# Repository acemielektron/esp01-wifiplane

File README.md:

# esp01-wifiplane

Here is the modified code and hardware for esp01 running [RAVI_BUTANI](https://www.instructables.com/member/RAVI_BUTANI/)'s cheapest diy [WIFI-CONTROLLED-RC-PLANE](https://www.instructables.com/id/WIFI-CONTROLLED-RC-PLANE/).

**Highlights**

* Hardware: Works on esp01's gpio0 and gpio2, both bootstrap pins require pullup on boot, so output is inverted

* Arduino code: Ability to invert outputs and switch gpio pins using define directives

* Android code: Now also works in home networks (for testing). A [compiled binary](ProcessingAndroidApp/wifiplane.apk) is supplied if you dont want to install processing and android sdk.

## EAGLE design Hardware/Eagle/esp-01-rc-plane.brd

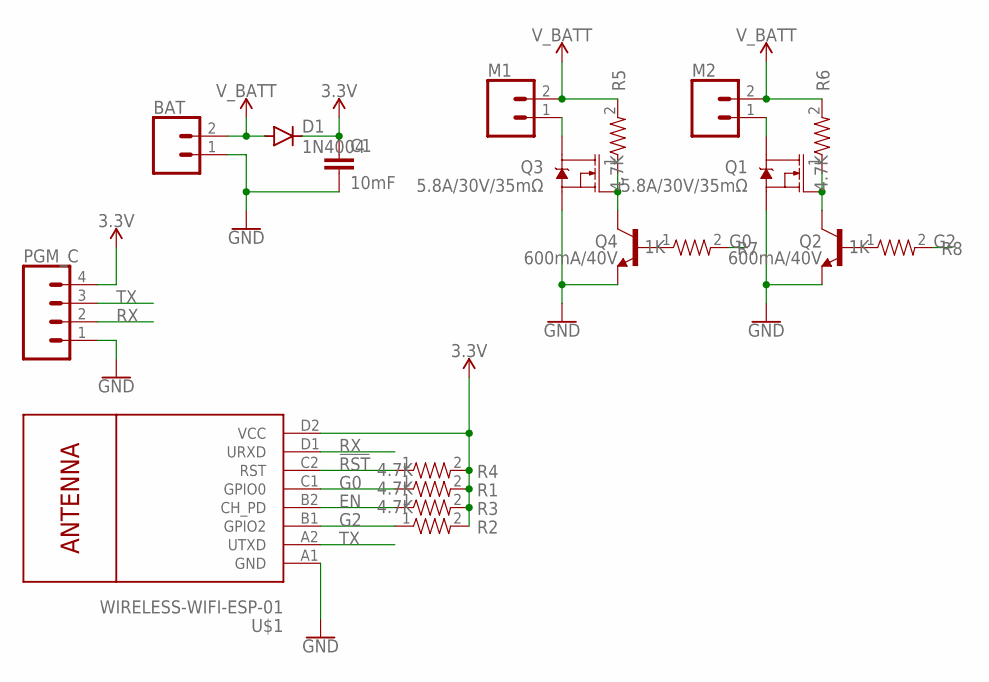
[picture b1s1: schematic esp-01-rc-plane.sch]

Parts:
BAT: CONN_02; 1X02
C1: 10mF; 0805
D1: 1N4004; DO41-10
M1, M2: CONN_02; 1X02
PGM_C: CONN_04; 1X04
Q1, Q3: 5.8A/30V/35mΩ; SOT23-3
Q2, Q4: 600mA/40V; SOT23-3
R1, R2, R3, R4, R5, R6: 4.7K; 0805
R7, R8: 1K; 0805
U$1: WIRELESS-WIFI-ESP-01

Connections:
3.3V: C1.1, D1.C, PGM_C.4, R1.2, R2.2, R3.2, R4.2, U$1.D2 (VCC)
!RST: R4.1, U$1.C2 (RST)
EN: R3.1, U$1.B2 (CH_PD)
G0: R1.1, R7.2, U$1.C1 (GPIO0)
G2: R2.1, R8.2, U$1.B1 (GPIO2)
GND: BAT.1, C1.2, PGM_C.1, Q1.2 (S), Q2.2 (E), Q3.2 (S), Q4.2 (E), U$1.A1 (GND)
unnamed: M1.1, Q3.3 (D)
unnamed: Q3.1 (G), Q4.3 (C), R5.1
unnamed: Q1.1 (G), Q2.3 (C), R6.1
unnamed: M2.1, Q1.3 (D)
unnamed: Q4.1 (B), R7.1
unnamed: Q2.1 (B), R8.1
RX: PGM_C.2, U$1.D1 (URXD)
TX: PGM_C.3, U$1.A2 (UTXD)
V_BATT: BAT.2, D1.A, M1.2, M2.2, R5.2, R6.2

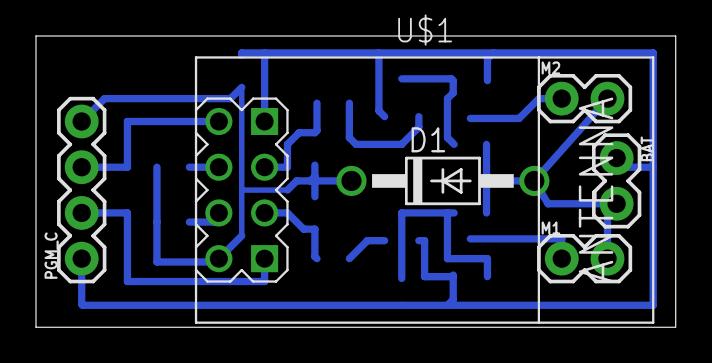
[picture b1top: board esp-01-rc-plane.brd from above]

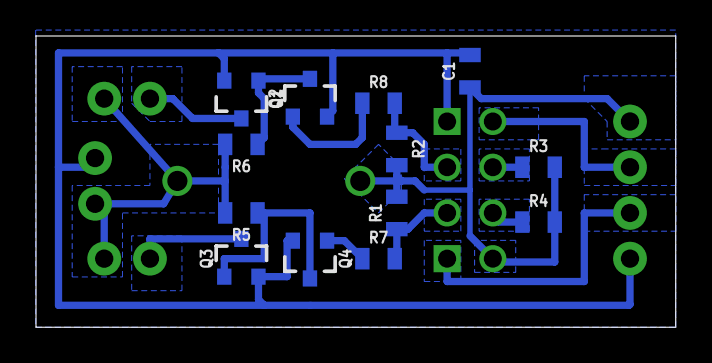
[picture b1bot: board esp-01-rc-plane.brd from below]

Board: 2 copper layers, 35.5 x 16.2 mm, 19 parts (13 on the bottom side), 15 nets.

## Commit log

2020-07-17 Original WIFI-CONTROLLED-RC-PLANE by RAVI_BUTANI https://www.instructables.com/id/WIFI-CONTROLLED-RC-PLANE/ Android source is at https://drive.google.com/file/d/1gKxi-3xPDlb2TV8EPb2U0kMg5PIsWq74/view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
2020-07-17 Electronics for esp01 (esp8266) Arduino sketch modified to work with esp01 Android app modified to work with local networks
2020-07-17 Update README.md
    Documentation update

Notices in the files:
parts and their libraries:
SparkFun-Connectors: Licensing: Creative Commons ShareAlike 4.0 International - https://creativecommons.org/licenses/by-sa/4.0
diy-modules: Released under the Creative Commons Attribution 4.0 International License: http://creativecommons.org/licenses/by/4.0
